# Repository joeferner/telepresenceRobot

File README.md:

Telepresence Robot
==================

After seeing a commercial for a Telepresence robot on TV, I knew I wanted to play with one, but after looking at prices I didn't want to pay for one.

I used an Android Nexus 7 tablet for the video conferencing. A custom PCB with an STM32 ARM processor and an FTDI USB chip to connect the Android tablet with the motors.

[Schematic](https://github.com/joeferner/telepresenceRobot/blob/master/hardware/main.pdf?raw=true)

Video
-----

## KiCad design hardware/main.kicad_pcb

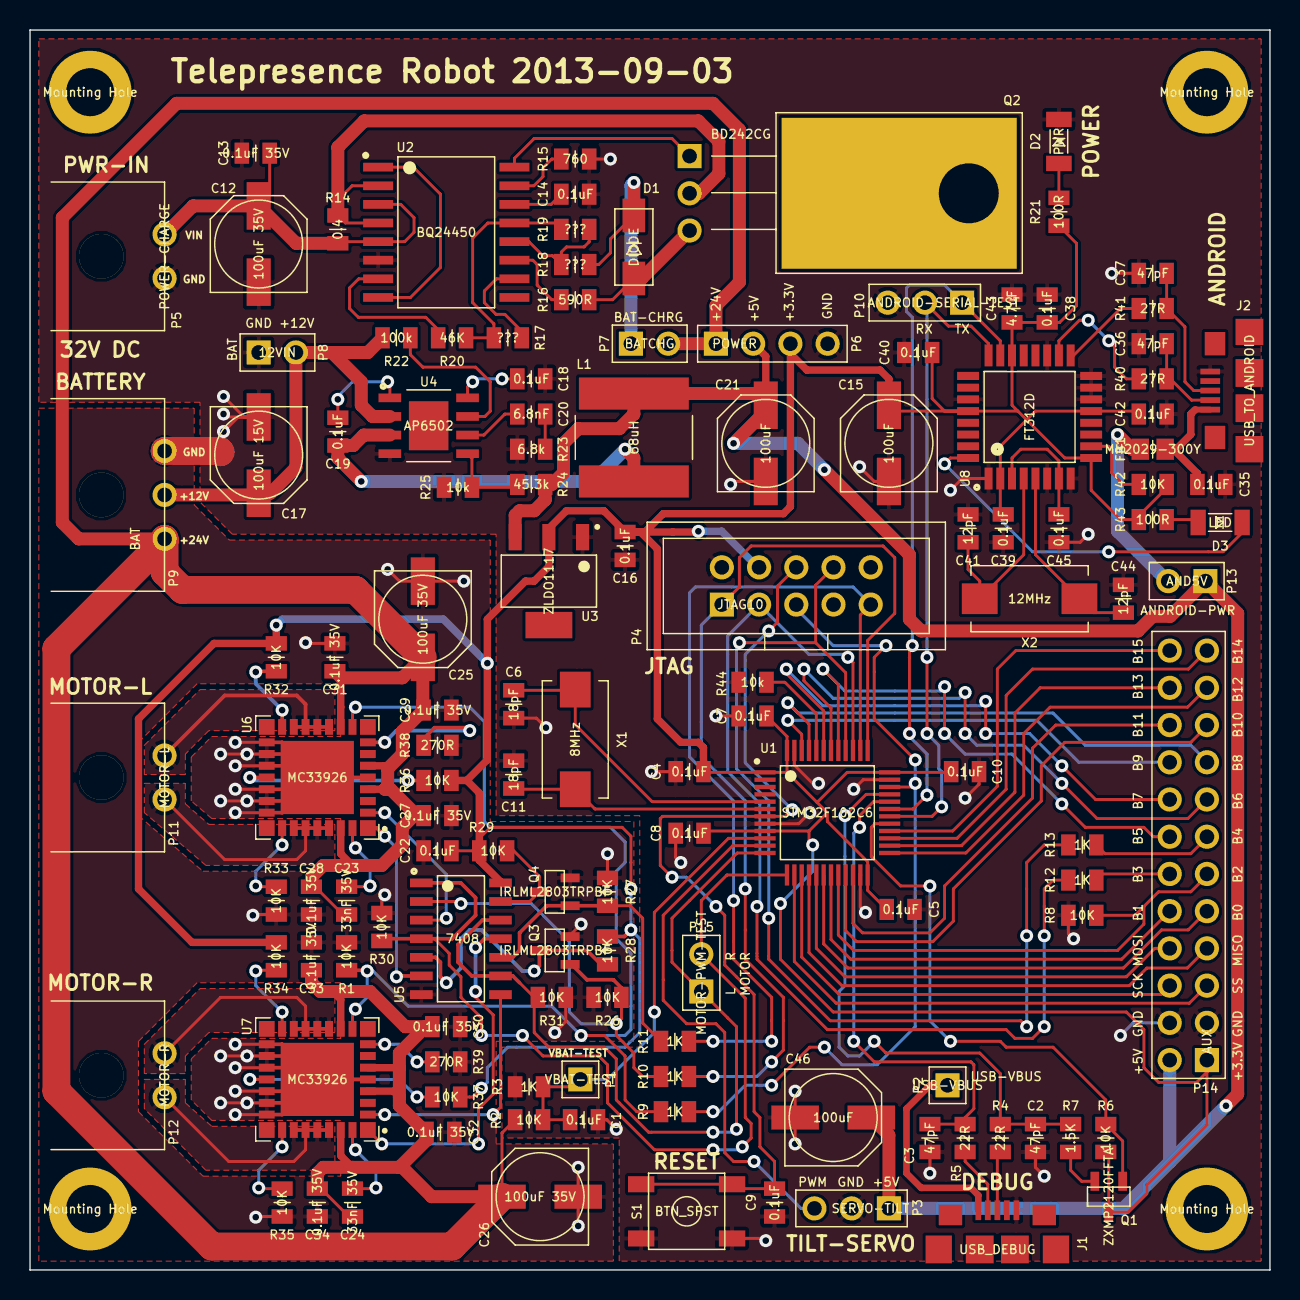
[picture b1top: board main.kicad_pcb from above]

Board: 2 copper layers, 84.6 x 84.6 mm, 133 parts (0 on the bottom side), 103 nets.

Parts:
BT1, BT2: BATTERY; EMPTY
C1, C4, C5, C7, C8, C9, C10, C14, C16, C18, C19, C22, C35, C38, C39, C40, C42, C45: 0.1uF; CAPC2012X100N
C2, C3, C36, C37: 47pF; CAPC2012X100N
C6, C11: 18pF; CAPC2012X100N
C12, C25, C26: 100uF 35V; CAPAE660X790N
C13, C27, C28, C29, C30, C31, C32, C33, C34: 0.1uF 35V; CAPC2012X100N
C15, C21, C46: 100uF; CAPAE660X790N
C17: 100uF 15V; CAPAE660X790N
C20: 6.8nF; CAPC2012X100N
C23, C24: 33nF 35V; CAPC2012X100N
C41, C44: 12pF; CAPC2012X100N
C43: 4.7uF; CAPC2012X100N
D1: DIODE; DIOM5226X220N
D2: PWR; LEDC3216X100N
D3: LED; LEDC3216X100N
FB1: MH2029-300Y; INDC2012X110N
J1: USB_DEBUG; JST_UB-MC5BR3-SD204-4S-NMP
J2: USB_TO_ANDROID; JST_UB-MC5BR3-SD204-4S-NMP
L1: 68uH; IND_ASPI-8040S-680M-T
M1, M2, M3, M4: Mounting Hole; MTGNP565H328Z565P
P1: VBAT-TEST; HDRV1W66P254_1X1_254X249X838P
P2: USB-VBUS; HDRV1W66P254_1X1_254X249X838P
P3: SERVO-TILT; HDRV3W66P254_1X3_762X249X838P
P4: JTAG10; SHDRV10W66P254_2X5_2035X870X609P
P5: POWER-CHARGE; TECONN-2-1445098-2
P6: POWER; HDRV4W66P254_1X4_1016X249X838P
P7: BATCHG; HDRV2W66P254_1X2_508X249X838P
P8: 12VIN; HDRV2W66P254_1X2_508X249X838P
P9: BAT; TECONN-2-1445098-3
P10: ANDROID-SERIAL-TEST; HDRV3W66P254_1X3_762X249X838P
P11: MOTOR-L; TECONN-2-1445098-2
P12: MOTOR-R; TECONN-2-1445098-2
P13: AND5V; HDRV2W66P254_1X2_508X249X838P
P14: AUX; HDRV24W66P254_2X12_3048X503X838P
P15: MOTOR-PWM-TEST; HDRV2W66P254_1X2_508X249X838P
Q1: ZXMP2120FFTA; SOT95P237X112_123-3N
Q2: BD242CG; TO254P1512X997X450-231-3P
Q3, Q4: IRLML2803TRPBF; SOT95P237X112_123-3N
R1, R2, R6, R8, R26, R27, R28, R29, R30, R31, R32, R33, R34, R35, R36, R37, R42: 10K; RESC2012X100N
R3, R9, R10, R11, R12, R13: 1K; RESC2012X100N
R4, R5: 22R; RESC2012X100N
R7: 1.5K; RESC2012X100N
R14: 0.4; RESC2012X100N
R15: 760; RESC2012X100N
R16: 590R; RESC2012X100N
R17, R18, R19: ???; RESC2012X100N
R20: 46K; RESC2012X100N
R21, R43: 100R; RESC2012X100N
R22: 100k; RESC2012X100N
R23: 6.8k; RESC2012X100N
R24: 45.3k; RESC2012X100N
R25, R44: 10k; RESC2012X100N
R38, R39: 270R; RESC2012X100N
R40, R41: 27R; RESC2012X100N
S1: BTN_SPST; CKCOMP-PTS525SM10SMTR
U1: STM32F102C6; QFP50P900X900X160-48N
U2: BQ24450; SOIC127P1030X265-16N
U3: ZLDO1117; SOT230P700X180-4N
U4: AP6502; SOIC127P600X150-9N
U5: 7408; SOIC127P600X175-14N
U6, U7: MC33926; PQFN80P800X800X220-33N
U8: FT312D; QFP80P900X900X160-32N
X1: 8MHz; XTAL8045X200N
X2: 12MHz; XTAL8045X200N

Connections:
+3.3V: C4.1, C5.1, C7.1, C8.1, C10.1, C15.1, C16.1, C22.1, C38.1, C39.1, C40.1, C42.1, C43.1, P4.4, P6.3, P14.1, Q1.3, R6.1, R21.1, R28.1, R29.1, R32.1, R34.1, R36.1, R37.1, R42.1, R43.1, U1.1, U1.9, U1.24, U1.36, U1.48, U3.2, U5.14, U8.2, U8.9, U8.13, U8.22, U8.28
+5V: C21.1, C46.1, L1.1, P3.1, P6.2, P13.1, P14.2, R24.2, U3.3
+12V: C17.1, P8.2, P9.2, R22.2, U4.2
+24V: C23.1, C24.1, C25.1, C26.1, C27.1, C28.1, C29.1, C30.1, C31.1, C32.1, C33.1, C34.1, P6.1, P7.2, P9.1, R2.1, U6.4, U6.6, U6.11, U6.31, U7.4, U7.6, U7.11, U7.31
/AUX-PB0: P14.9, U1.18
/AUX-PB1: P14.10, U1.19
/AUX-PB2: P14.11, R8.1, U1.20
/AUX-PB3: P14.12, R12.2
/AUX-PB4: P14.13, R13.2
/AUX-PB5: P14.14, U1.41
/AUX-PB6: P14.15, U1.42
/AUX-PB7: P14.16, U1.43
/AUX-PB8: P14.17, U1.45
/AUX-PB9: P14.18, U1.46
/AUX-PB10: P14.19, U1.21
/AUX-PB11: P14.20, U1.22
/AUX-PB12: P14.21, U1.25
/AUX-PB13: P14.22, U1.26
/AUX-PB14: P14.23, U1.27
/AUX-PB15: P14.24, U1.28
/AUX-SPI-MISO: P14.7, U1.16
/AUX-SPI-MOSI: P14.8, U1.17
/AUX-SPI-SCK: P14.6, U1.15
/AUX-SPI-SS: P14.5, U1.14
/Android/RX: P10.2, U1.30, U8.24
/Android/TX: P10.1, U1.31, U8.23
/JNTRST: P4.8, R13.1, U1.40
/JTCK: P4.1, R10.1, U1.37
/JTDI: P4.9, R11.1, U1.38
/JTDO: P4.3, R12.1, U1.39
/JTMS: P4.5, R9.1, U1.34
/Motor Controllers/EN: R1.1, R9.2, U6.10, U7.10
/Motor Controllers/MOTOR-L-DIR: Q3.1, R10.2, R26.1, U5.2
/Motor Controllers/MOTOR-L-OUT1: P11.2, U6.12, U6.13, U6.14, U6.15
/Motor Controllers/MOTOR-L-OUT2: P11.1, U6.27, U6.28, U6.29, U6.30
/Motor Controllers/MOTOR-L-PWM: P15.2, R30.1, U1.13, U5.1, U5.4
/Motor Controllers/MOTOR-R-DIR: Q4.1, R11.2, R27.1, U5.10
/Motor Controllers/MOTOR-R-OUT1: P12.2, U7.12, U7.13, U7.14, U7.15
/Motor Controllers/MOTOR-R-OUT2: P12.1, U7.27, U7.28, U7.29, U7.30
/Motor Controllers/MOTOR-R-PWM: P15.1, R31.1, U1.12, U5.9, U5.12
/Power/VIN+: C12.1, C13.1, P5.2, R14.1, U2.3, U2.5
/SERVO-TILT-PWM: P3.3, U1.11
/USB-DISCONNECT: Q1.1, R6.2, U1.29
/VBAT-TEST: C1.1, P1.1, R2.2, R3.1, U1.10
/nRST: C9.1, P4.6, S1.3, S1.4, U1.7
GND: C1.2, C2.2, C3.2, C4.2, C5.2, C6.2, C7.2, C8.2, C9.2, C10.2, C11.2, C12.2, C13.2, C14.2, C15.2, C16.2, C17.2, C18.2, C21.2, C22.2, C25.2, C26.2, C27.2, C28.2, C29.2, C30.2, C31.2, C32.2, C33.2, C34.2, C35.2, C36.2, C37.2, C38.2, C39.2, C40.2, C41.2, C42.2, C43.2, C44.2, C45.2, C46.2, D2.2, J1.5, J2.5, P3.2, P4.2, P5.1, P6.4, P8.1, P9.3, P10.3, P14.3, P14.4, Q3.2, Q4.2, R1.2, R3.2, R8.2, R15.1, R23.1, R25.1, R26.2, R27.2, R30.2, R31.2, R33.2, R35.2, R38.2, R39.2, R44.2, S1.1, S1.2, U1.8, U1.23, U1.35, U1.47, U2.6, U3.1, U4.4, U5.7, U6.5, U6.18, U6.19, U6.20, U6.22, U6.23, U6.24, U6.33, U7.5, U7.18, U7.19, U7.20, U7.22, U7.23, U7.24, U7.33, U8.1, U8.6, U8.8, U8.14, U8.15, U8.16, U8.19, U8.27
unnamed: C2.1, R4.1, R7.2, U1.33
unnamed: C3.1, R5.1, U1.32
unnamed: C6.1, U1.5, X1.2
unnamed: C11.1, U1.6, X1.1
unnamed: C14.1, U2.14
unnamed: C18.1, U4.8
unnamed: C19.1, U4.1
unnamed: C19.2, L1.2, U4.3
unnamed: C20.1, U4.6
unnamed: C20.2, R23.2
unnamed: C23.2, U6.32
unnamed: C24.2, U7.32
unnamed: C35.1, FB1.1, J2.1
unnamed: C36.1, J2.2, R40.2
unnamed: C37.1, J2.3, R41.2
unnamed: C41.1, U8.4, X2.2
unnamed: C44.1, U8.5, X2.1
unnamed: C45.1, U8.3, U8.7
unnamed: D1.1, Q2.1, R16.2
unnamed: D1.2, P7.1, R18.2
unnamed: D2.1, R21.2
unnamed: D3.1, R43.2
unnamed: D3.2, U8.32
unnamed: FB1.2, P13.2
unnamed: J1.1, P2.1
unnamed: J1.2, R5.2
unnamed: J1.3, R4.2
unnamed: Q1.2, R7.1
unnamed: Q2.2, U2.16
unnamed: Q2.3, R14.2, U2.2, U2.4
unnamed: Q3.3, R28.2, U5.5
unnamed: Q4.3, R29.2, U5.13
unnamed: R15.2, U2.15
unnamed: R16.1, U2.11
unnamed: R17.1, R19.1, R20.2, U2.13
unnamed: R17.2, U2.10
unnamed: R18.1, R19.2, U2.12
unnamed: R20.1, U2.7
unnamed: R22.1, U4.7
unnamed: R24.1, R25.2, U4.5
unnamed: R32.2, U6.16
unnamed: R33.1, U6.26
unnamed: R34.2, U7.16
unnamed: R35.1, U7.26
unnamed: R36.2, U6.21
unnamed: R37.2, U7.21
unnamed: R38.1, U6.8
unnamed: R39.1, U7.8
unnamed: R40.1, U8.18
unnamed: R41.1, U8.17
unnamed: R42.2, U8.10
unnamed: R44.1, U1.44
unnamed: U2.1, U2.8
unnamed: U5.3, U6.2
unnamed: U5.6, U6.1
unnamed: U5.8, U7.2
unnamed: U5.11, U7.1

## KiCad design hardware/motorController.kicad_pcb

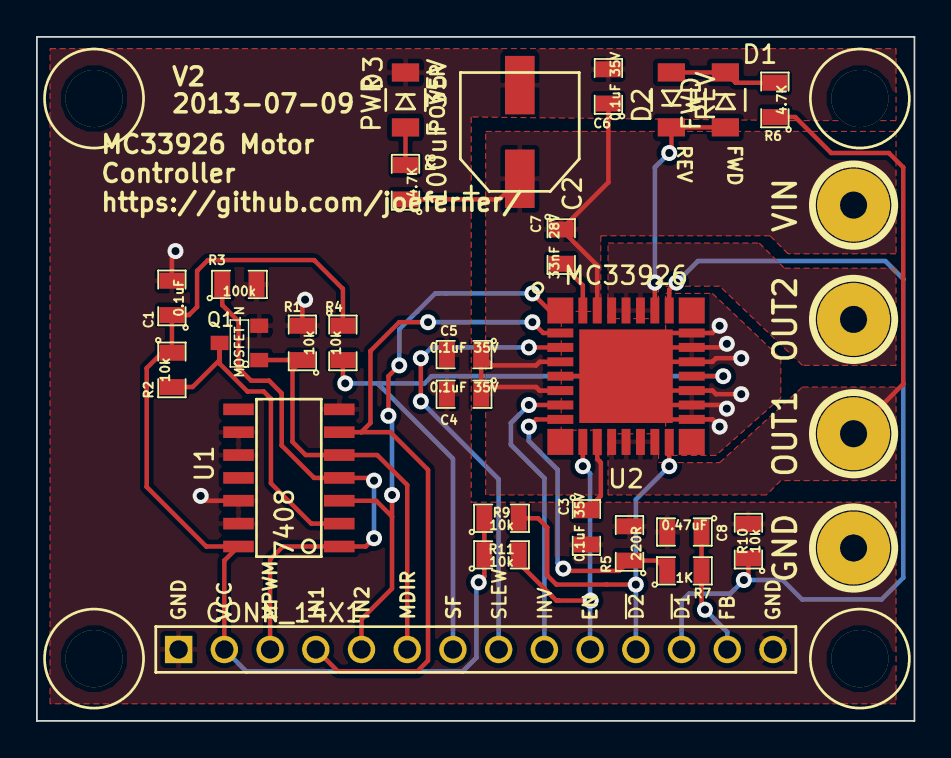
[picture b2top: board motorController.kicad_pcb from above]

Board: 2 copper layers, 48.8 x 38.0 mm, 34 parts (0 on the bottom side), 21 nets.

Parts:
C1: 0.1uF; SM0805
C2: 100uF 35V; CAP-CAN-6.30mm
C3, C4, C5, C6: 0.1uF 35V; SM0805
C7: 33nF 28V; SM0805
C8: 0.47uF; SM0805
D1: FWD; LED-1206
D2: REV; LED-1206
D3: PWR; LED-1206
J1: CONN_14X1; PIN_ARRAY_14X1
M1, M2, M3, M4: Mounting Hole; MOUNTING_HOLE_0.125in
P1, P2, P3, P4: CONN_1; 1pin
Q1: MOSFET-N; SOT23
R1, R2, R4, R9, R10, R11: 10k; SM0805
R3: 100k; SM0805
R5: 220R; SM0805
R6, R8: 4.7K; SM0805
R7: 1K; SM0805
U1: 7408; SOIC14_3.9mm
U2: MC33926; QFN-PWR-8X8

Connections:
/D1#: J1.12, R10.1, U2.26
/D2#: J1.11, R9.2, U2.16
/EN: J1.10, R11.2, U2.10
/FB: C8.1, J1.13, R7.2
/IN1: J1.4, U1.6, U2.2
/IN2: J1.5, U1.3, U2.1
/INV: J1.9, U2.7
/MDIR: J1.6, Q1.1, R1.1, U1.5
/MPWM: J1.3, R3.1, U1.1, U1.4
/OUT1: P2.1, R6.1, U2.12, U2.13, U2.14, U2.15
/OUT2: D1.1, D2.2, P3.1, U2.27, U2.28, U2.29, U2.30
/SF: J1.7, R4.2, U2.21
/SLEW: J1.8, U2.3
GND: C1.2, C2.2, C3.2, C4.2, C5.2, C6.2, C8.2, D3.2, J1.1, J1.14, P4.1, Q1.2, R1.2, R3.2, R5.2, R10.2, U1.7, U1.9, U1.10, U1.12, U1.13, U2.5, U2.18, U2.19, U2.20, U2.22, U2.23, U2.24, U2.33
unnamed: D3.1, R8.2
unnamed: D1.2, D2.1, R6.2
unnamed: R5.1, R7.1, U2.8
unnamed: C7.2, U2.32
unnamed: Q1.3, R2.2, U1.2
VCC: C1.1, J1.2, R2.1, R4.1, R9.1, R11.1, U1.14
VDD: C2.1, C3.1, C4.1, C5.1, C6.1, C7.1, P1.1, R8.1, U2.4, U2.6, U2.11, U2.31

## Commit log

2013-06-04 initial
2013-06-04 update model numbers
2013-06-06 motor controller
2013-06-06 silk
2013-06-09 plot
2013-06-10 v1 motor controller
2013-06-15 working blink
2013-06-15 auto upload
2013-06-15 add upload to build
2013-06-16 initial cut at virtual serial port
2013-06-16 moved firmware
2013-06-16 ignore netbeans project
2013-06-18 more
2013-06-19 getting further
2013-06-20 usart
2013-06-20 working debug out
2013-06-21 more logging
2013-06-21 working coms
2013-06-26 working virtual serial port
2013-06-26 refactoring code
2013-06-27 refactor
2013-06-27 refactor usb code
2013-06-27 multicast
2013-06-27 working multicast
2013-06-27 initial android
2013-06-27 initial layout
2013-06-27 initial coms
2013-06-29 maybe working coms
2013-06-29 using set speed
2013-06-30 initial time work
2013-07-03 working coms with android
2013-07-05 acceleration/deceleration and safety
2013-07-05 motor work startedg
2013-07-05 working motor pwm
2013-07-05 remap io to free up all of port B for user io
2013-07-05 added command to turn on and off status led
2013-07-07 initial server
2013-07-07 working send
2013-07-09 fixed pin numbering on motor controller
2013-07-09 simplified server
2013-07-13 wheel
2013-07-13 motor bracket
2013-07-13 motor
2013-07-13 rename
2013-07-13 motor wheel assembly
2013-07-14 basic robot
2013-07-14 support and materials
2013-07-16 casters
2013-07-16 tablet mount
2013-08-02 add pullups to motorcontroller
2013-08-02 main board work
2013-08-02 increate pwm frequency
2013-08-05 working web to android
2013-08-05 added joystick
2013-08-09 initial cut at speed alg
2013-08-09 almost working
2013-08-10 main schematic work
2013-08-10 fix package.json repository
2013-08-12 make compatible with java 6
2013-08-12 make speed control modular and try another algorithm
2013-08-14 schematic updates
2013-08-14 added servo support
2013-08-14 battery voltage
2013-08-20 updates to mechanical
2013-08-21 update schematic
2013-08-27 initial new.mod
2013-08-27 2-pin header
2013-08-27 more pcb work
2013-08-27 support update from kicad-library
2013-08-27 update net
2013-08-28 button
2013-08-28 qfp48
2013-08-28 soic16
2013-08-29 more footprints
2013-08-30 new packages
2013-08-30 pqfn
2013-08-30 inductor
2013-08-30 new pcb
2013-09-01 layout
2013-09-02 layout no unconnected
2013-09-03 added border and larger traces
2013-09-03 moved labels. increased power widths
2013-09-03 power track width, ground plane connects
2013-09-03 moved motor controller to breakout boards
2013-09-03 don't update on save
2013-09-03 update mod file
2013-09-03 v1 update
2013-09-03 rotated jtag header
2013-09-03 v1 final
2013-09-10 add kicad-library as git subtree
2013-09-10 fix save and update kicad-library to use subtree
2013-09-12 moved comments to seperate files
2013-09-12 removed comments from mod file
2013-09-23 calculations for battery charger
2013-09-29 working com connection
2013-09-29 renamed debug funcations to android
2013-09-29 changed product name
2013-09-29 changed silk size
2013-09-29 reformat usb files
2013-09-29 refactor while loop into function
2013-09-29 sync from library
2013-10-04 fix server
2013-10-06 fixed 'O' bridge to be printable
2013-10-06 redesign mount
2013-10-06 removed unused parts
2013-10-06 added mast tolerance
2013-10-06 font
2013-10-06 Created holder control part
2013-10-09 increase power track thickness
2013-10-11 major refactor
2013-10-11 refactor robot
2013-10-11 foreground service
2013-10-11 settings
2013-10-12 exit pref
2013-10-12 cleaner close
2013-10-12 logging
2013-10-12 handle non printable characters
2013-10-13 battery latch
2013-10-14 refactor logs
2013-10-16 refactor and added battery level
2013-10-16 fix connect issue
2013-11-06 added tilt control
2013-11-13 stop servo after x time
2013-11-21 working
2013-11-21 moved converter
2013-11-21 changed to using sockets on Android instead of web sockets
2013-11-22 fix speed control
2013-11-22 initial client commit
2013-11-22 working qt client
2013-11-22 enable/disable logging
2013-11-22 don't log so much
2013-11-22 better mouse handling
2013-11-22 fix mouse location and added crosshairs
2013-11-22 cut speed in half
2014-08-08 add pdf of schematic
2014-08-08 add schematic link
